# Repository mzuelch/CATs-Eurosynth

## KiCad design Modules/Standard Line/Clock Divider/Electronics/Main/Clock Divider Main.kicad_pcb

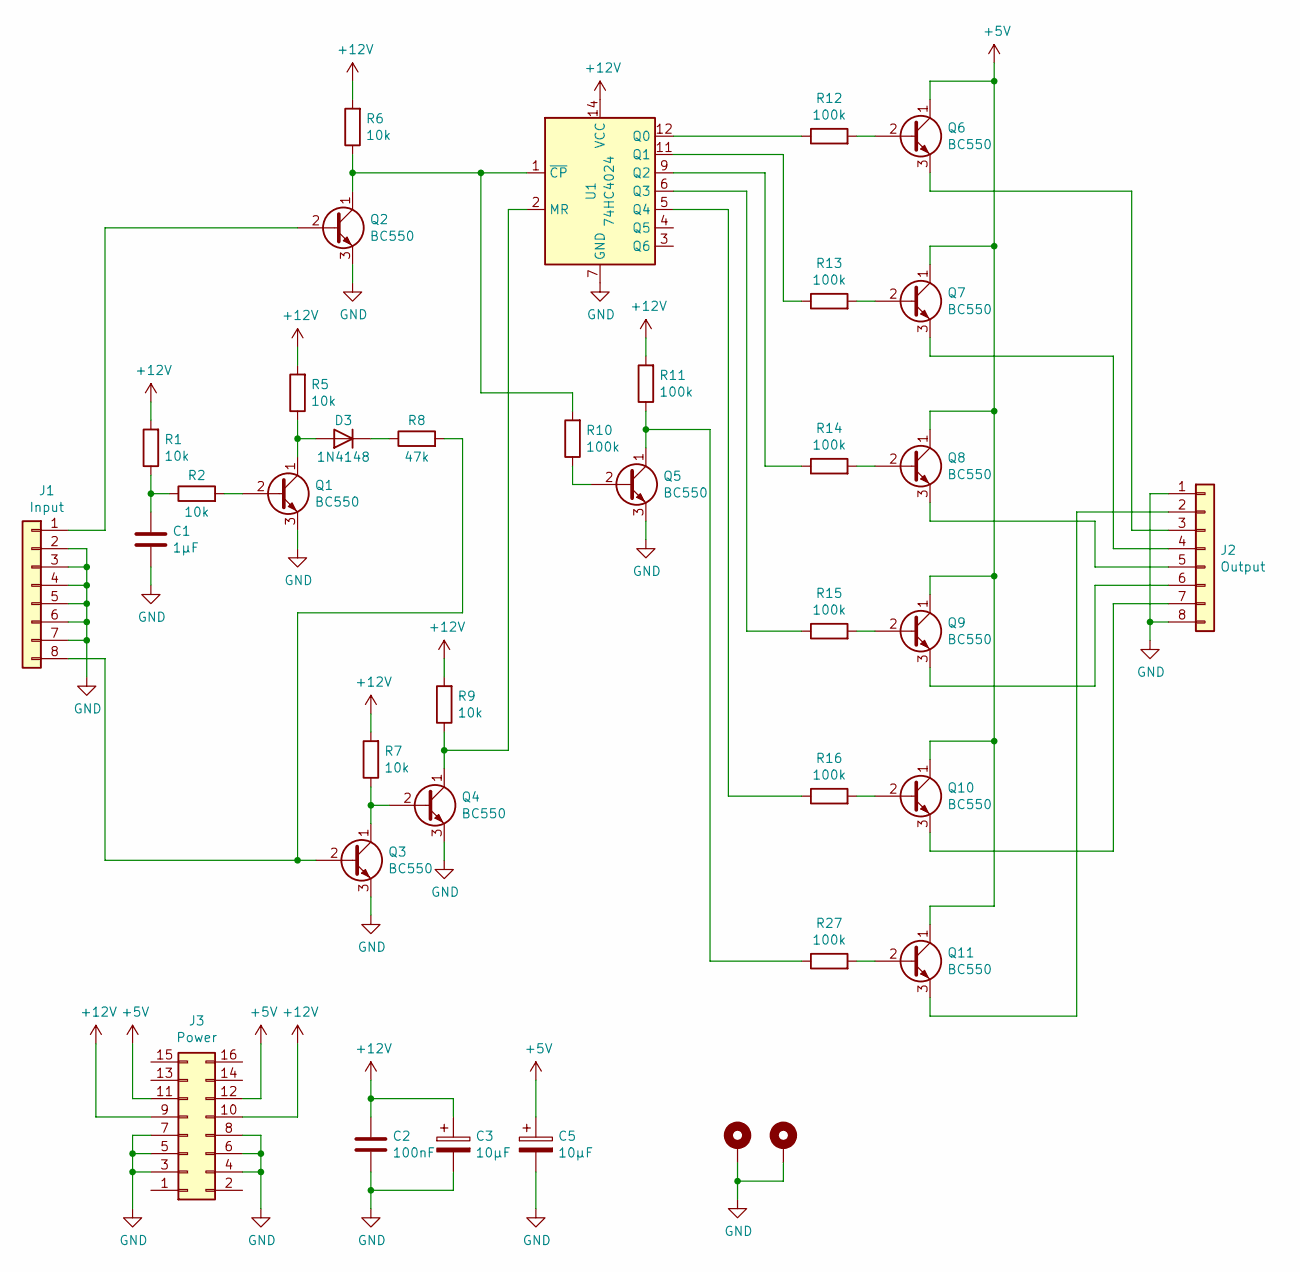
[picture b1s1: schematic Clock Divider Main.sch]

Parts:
C1: 1µF; C_Disc_D6.0mm_W2.5mm_P5.00mm
C2: 100nF; C_Disc_D5.0mm_W2.5mm_P5.00mm
C3, C5: 10µF; CP_Radial_D5.0mm_P2.50mm
D3: 1N4148; D_DO-35_SOD27_P7.62mm_Horizontal
H1, H2: MountingHole_Pad; MountingHole_2.7mm_M2.5_DIN965_Pad
J1: Input; PinHeader_1x08_P2.54mm_Vertical
J2: Output; PinHeader_1x08_P2.54mm_Vertical
J3: Power; IDC-Header_2x08_P2.54mm_Vertical
Q1, Q2, Q3, Q4, Q5, Q6, Q7, Q8, Q9, Q10, Q11: BC550; TO-92_Inline
R1, R2, R5, R6, R7, R9: 10k; R_Axial_DIN0207_L6.3mm_D2.5mm_P7.62mm_Horizontal
R8: 47k; R_Axial_DIN0207_L6.3mm_D2.5mm_P7.62mm_Horizontal
R10, R11, R12, R13, R14, R15, R16, R27: 100k; R_Axial_DIN0207_L6.3mm_D2.5mm_P7.62mm_Horizontal
U1: 74HC4024; DIP-14_W7.62mm_LongPads

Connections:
+5V: C5.1, J3.11, J3.12, Q6.1 (C), Q7.1 (C), Q8.1 (C), Q9.1 (C), Q10.1 (C), Q11.1 (C)
+12V: C2.1, C3.1, J3.9, J3.10, R1.2, R5.2, R6.2, R7.2, R9.2, R11.2, U1.14 (VCC)
GND: C1.2, C2.2, C3.2, C5.2, H1.1, H2.1, J1.2, J1.3, J1.4, J1.5, J1.6, J1.7, J2.1, J2.8, J3.3, J3.4, J3.5, J3.6, J3.7, J3.8, Q1.3 (E), Q2.3 (E), Q3.3 (E), Q4.3 (E), Q5.3 (E), U1.7 (GND)
unnamed: C1.1, R1.1, R2.1
unnamed: D3.1 (K), R8.1
unnamed: D3.2 (A), Q1.1 (C), R5.1
unnamed: J1.1, Q2.2 (B)
unnamed: J1.8, Q3.2 (B), R8.2
unnamed: J2.2, Q11.3 (E)
unnamed: J2.3, Q6.3 (E)
unnamed: J2.4, Q7.3 (E)
unnamed: J2.5, Q8.3 (E)
unnamed: J2.6, Q9.3 (E)
unnamed: J2.7, Q10.3 (E)
unnamed: Q1.2 (B), R2.2
unnamed: Q2.1 (C), R6.1, R10.2, U1.1 (~CP)
unnamed: Q3.1 (C), Q4.2 (B), R7.1
unnamed: Q4.1 (C), R9.1, U1.2 (MR)
unnamed: Q5.1 (C), R11.1, R27.1
unnamed: Q5.2 (B), R10.1
unnamed: Q6.2 (B), R12.2
unnamed: Q7.2 (B), R13.2
unnamed: Q8.2 (B), R14.2
unnamed: Q9.2 (B), R15.2
unnamed: Q10.2 (B), R16.2
unnamed: Q11.2 (B), R27.2
unnamed: R12.1, U1.12 (Q0)
unnamed: R13.1, U1.11 (Q1)
unnamed: R14.1, U1.9 (Q2)
unnamed: R15.1, U1.6 (Q3)
unnamed: R16.1, U1.5 (Q4)

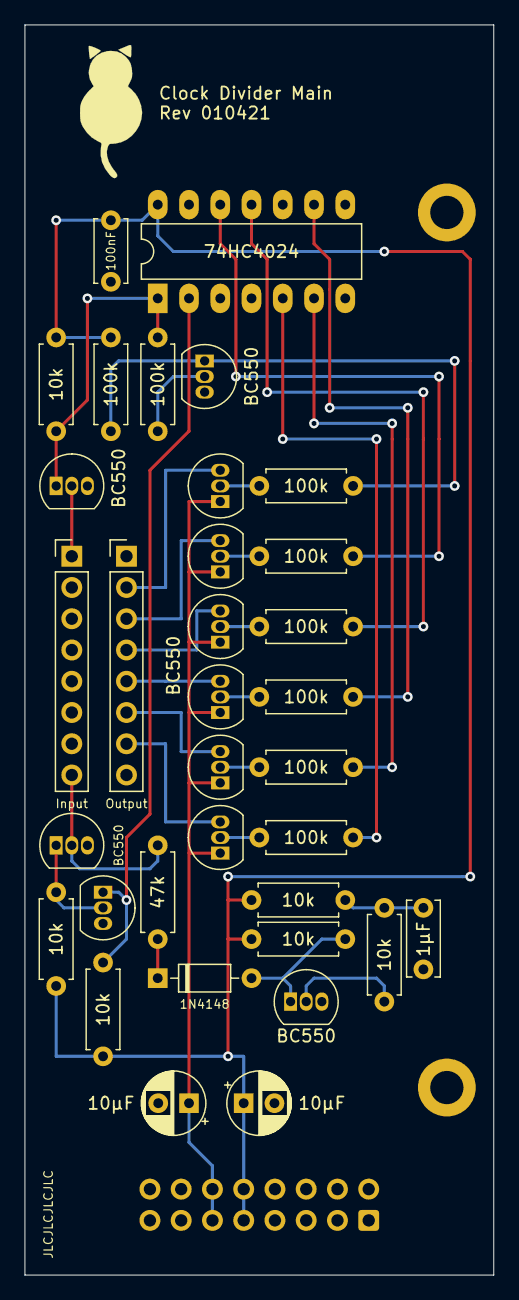
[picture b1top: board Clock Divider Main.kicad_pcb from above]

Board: 2 copper layers, 38.1 x 101.6 mm, 37 parts (1 on the bottom side), 31 nets.

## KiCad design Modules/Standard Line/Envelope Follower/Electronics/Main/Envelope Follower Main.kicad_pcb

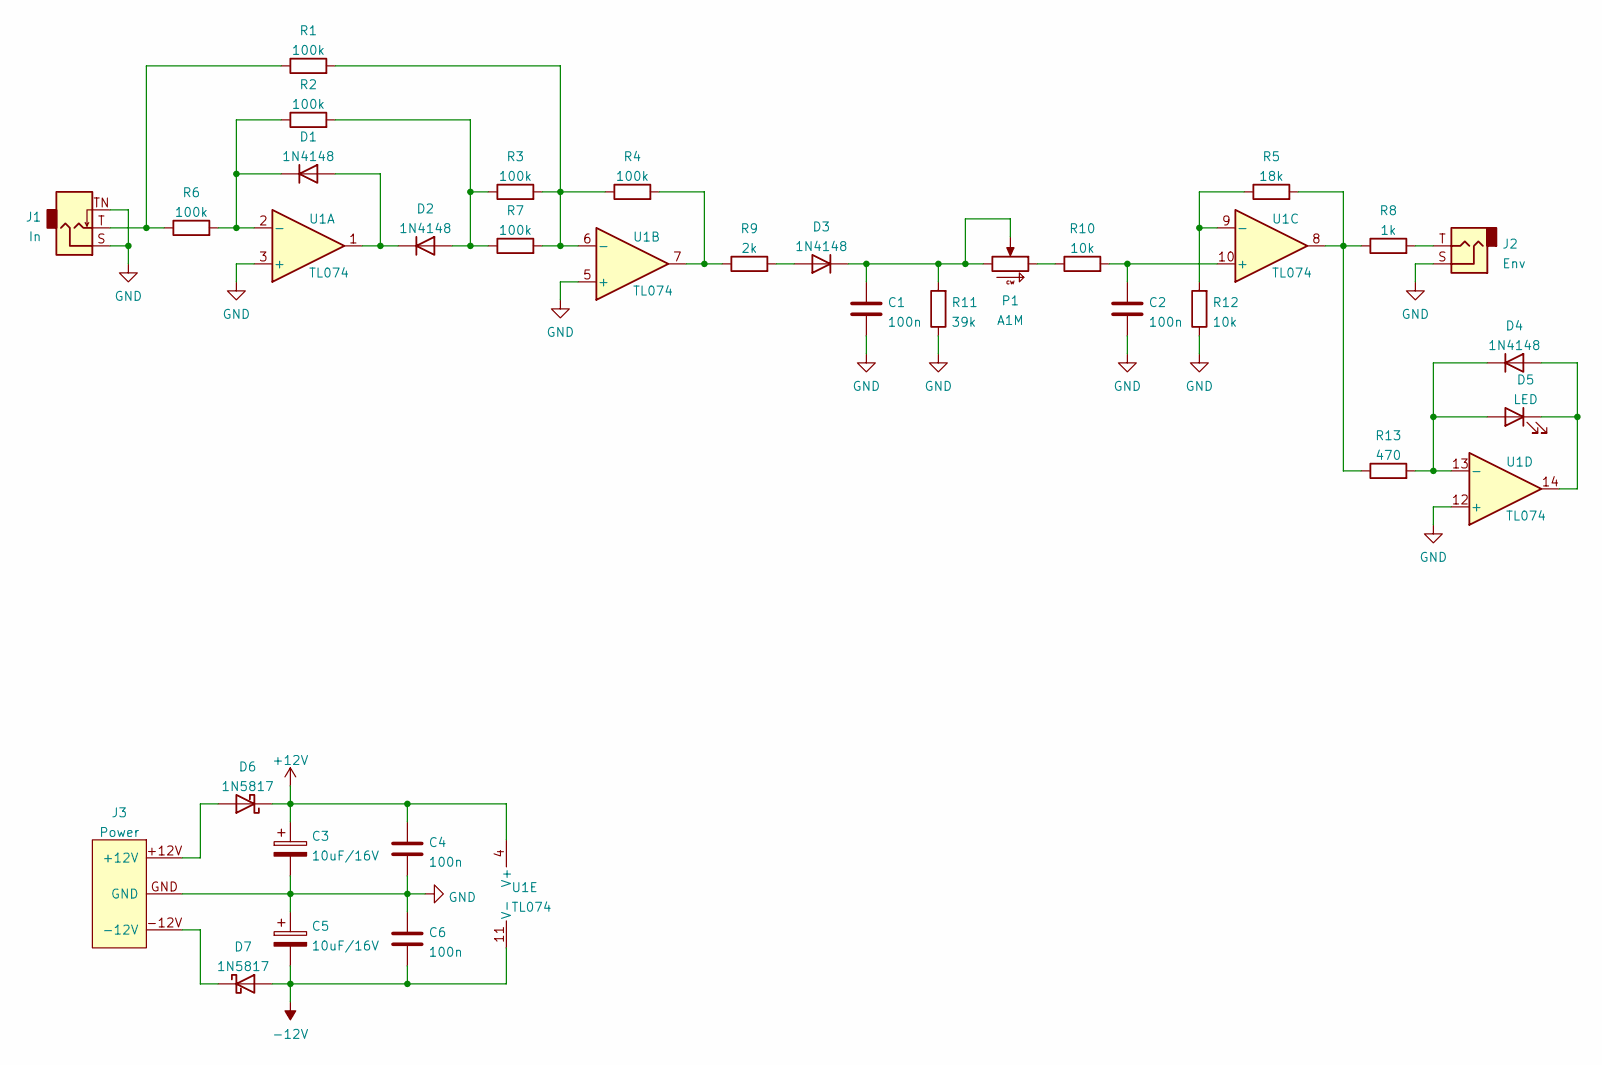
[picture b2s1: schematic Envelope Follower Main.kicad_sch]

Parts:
C1, C2, C4, C6: 100n; C_Disc_D4.7mm_W2.5mm_P5.00mm
C3, C5: 10uF/16V; CP_Radial_D5.0mm_P2.00mm
D1, D2, D3, D4: 1N4148; D_DO-35_SOD27_P7.62mm_Horizontal
D5: LED; LED_D3.0mm_Horizontal_O1.27mm_Z10.0mm
D6, D7: 1N5817; D_DO-41_SOD81_P10.16mm_Horizontal
J1: In; Jack_3.5mm_QingPu_WQP-PJ323M
J2: Env; Jack_3.5mm_QingPu_WQP-PJ323M
J3: Power; Power_2x5_Vertical
P1: A1M; Potentiometer_AlpsAlpine_RK0971110
R1, R2, R3, R4, R6, R7: 100k; R_Axial_DIN0207_L6.3mm_D2.5mm_P7.62mm_Horizontal
R5: 18k; R_Axial_DIN0207_L6.3mm_D2.5mm_P7.62mm_Horizontal
R8: 1k; R_Axial_DIN0207_L6.3mm_D2.5mm_P7.62mm_Horizontal
R9: 2k; R_Axial_DIN0207_L6.3mm_D2.5mm_P7.62mm_Horizontal
R10, R12: 10k; R_Axial_DIN0207_L6.3mm_D2.5mm_P7.62mm_Horizontal
R11: 39k; R_Axial_DIN0207_L6.3mm_D2.5mm_P7.62mm_Horizontal
R13: 470; R_Axial_DIN0207_L6.3mm_D2.5mm_P7.62mm_Horizontal
U1: TL074; DIP-14_W7.62mm_LongPads

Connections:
+12V: C3.1, C4.1, D6.1 (K), U1.4 (V+)
-12V: C5.2, C6.2, D7.2 (A), U1.11 (V-)
GND: C1.2, C2.2, C3.2, C4.2, C5.1, C6.1, J1.S, J1.TN, J2.S, J3.GND, R11.1, R12.1, U1.3 (+), U1.5 (+), U1.12 (+)
unnamed: C1.1, D3.1 (K), P1.CCW, P1.W, R11.2
unnamed: C2.1, R10.2, U1.10 (+)
unnamed: D1.1 (K), R2.1, R6.2, U1.2 (-)
unnamed: D1.2 (A), D2.1 (K), U1.1
unnamed: D2.2 (A), R2.2, R3.1, R7.1
unnamed: D3.2 (A), R9.2
unnamed: D4.1 (K), D5.2 (A), R13.2, U1.13 (-)
unnamed: D4.2 (A), D5.1 (K), U1.14
unnamed: D6.2 (A), J3.+12V
unnamed: D7.1 (K), J3.-12V
unnamed: J1.T, R1.1, R6.1
unnamed: J2.T, R8.2
unnamed: P1.CW, R10.1
unnamed: R1.2, R3.2, R4.1, R7.2, U1.6 (-)
unnamed: R4.2, R9.1, U1.7
unnamed: R5.1, R12.2, U1.9 (-)
unnamed: R5.2, R8.1, R13.1, U1.8

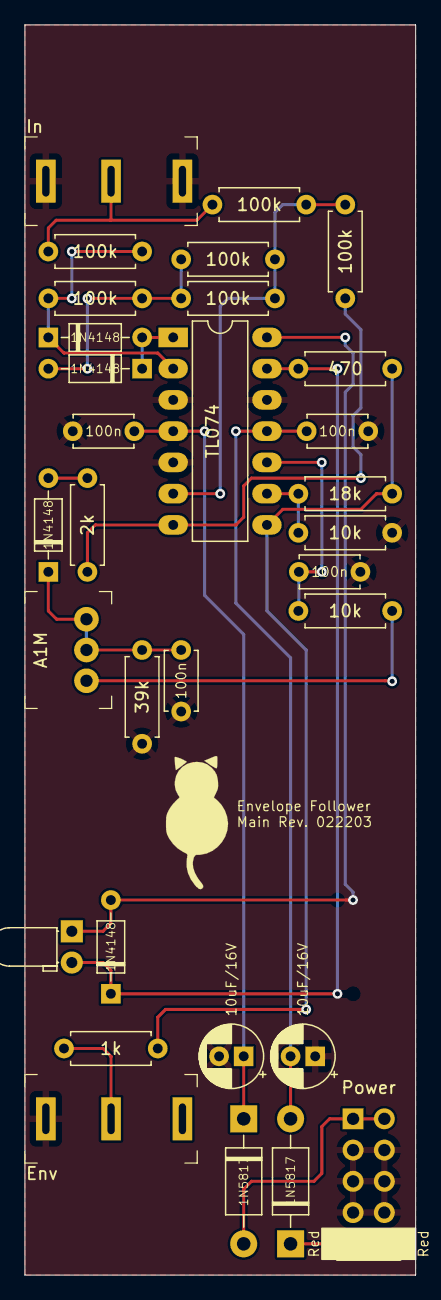
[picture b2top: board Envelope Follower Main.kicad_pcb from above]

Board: 2 copper layers, 31.8 x 101.6 mm, 31 parts (0 on the bottom side), 20 nets.

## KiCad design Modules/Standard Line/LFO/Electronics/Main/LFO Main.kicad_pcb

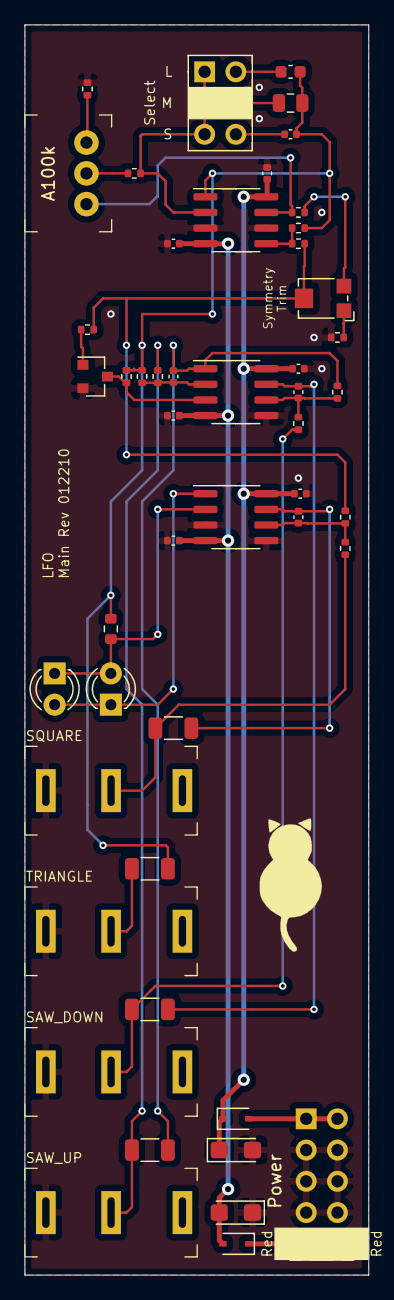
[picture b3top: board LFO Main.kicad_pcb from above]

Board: 2 copper layers, 27.9 x 101.6 mm, 49 parts (0 on the bottom side), 31 nets.

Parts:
C1: 1µF; C_0402_1005Metric
C2, C3: 10µF; CP_EIA-3216-18_Kemet-A
C4, C5, C6, C7, C8, C9: 100n; C_0402_1005Metric
C10: 10µF; C_0603_1608Metric
C11: 2.2µF; C_0805_2012Metric
C12, C13, C14: 10p; C_0402_1005Metric
D1, D2: LED; LED_D3.0mm
D3, D4: 1N5819WS; D_SOD-323
J1: SAW_UP; Jack_3.5mm_QingPu_WQP-PJ323M
J2: SAW_DOWN; Jack_3.5mm_QingPu_WQP-PJ323M
J3: TRIANGLE; Jack_3.5mm_QingPu_WQP-PJ323M
J4: SQUARE; Jack_3.5mm_QingPu_WQP-PJ323M
J5: Power; Power_2x5_Vertical
J6: Select; PinHeader_2x03_P2.54mm_Vertical
Q1: MMBT3904; SOT-23
R1: 47; R_0402_1005Metric
R2: 68k; R_0402_1005Metric
R4, R5, R9, R10, R11, R13, R14, R19, R20: 100k; R_0402_1005Metric
R6, R7: 2k; R_0402_1005Metric
R8: 47k; R_0402_1005Metric
R12, R15, R16, R17: 1k; R_1206_3216Metric
R18: 2k7; R_0603_1608Metric
RV1: A100k; Potentiometer_AlpsAlpine_RK0971110
T1: 1k; Potentiometer_Bourns_TC33X_Vertical
U1, U2, U3: TL072; SOIC-8_3.9x4.9mm_P1.27mm

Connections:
+12V: C2.1, C4.1, C6.1, C8.1, D3.1, U1.8, U2.8, U3.8
+12VA: D3.2, J5.+12V
-12V: C3.2, C5.2, C7.2, C9.2, D4.2, U1.4, U2.4, U3.4
-12VA: D4.1, J5.-12V
GND: C2.2, C3.1, C4.2, C5.1, C6.2, C7.1, C8.2, C9.1, J1.S, J2.S, J3.S, J4.S, J5.GND, Q1.2, R1.1, R7.1, U1.3, U1.6, U2.5, U3.3, U3.5
unnamed: C1.2, J6.6
unnamed: C10.2, J6.2
unnamed: C11.2, J6.4
unnamed: C12.1, R12.2, R14.2, U2.1
unnamed: C12.2, R9.1, R11.2, U2.2
unnamed: C13.1, R15.2, U2.7
unnamed: C13.2, R13.2, R14.1, U2.6
unnamed: C14.1, R17.2, U3.7
unnamed: C14.2, R19.2, R20.1, U3.6
unnamed: D1.1, D2.2, U3.1
unnamed: D1.2, D2.1, R18.2, U3.2
unnamed: J1.T, R11.1, R12.1
unnamed: J2.T, R13.1, R15.1
unnamed: J3.T, R16.1
unnamed: J4.T, R17.1, R19.1
unnamed: J6.1, J6.3, J6.5, R2.1, U1.2
unnamed: Q1.1, R8.1
unnamed: Q1.3, R10.1, U2.3
unnamed: R1.2, RV1.CCW
unnamed: R2.2, RV1.W
unnamed: R4.1, R5.2, U1.5
unnamed: R6.1, T1.3
unnamed: R6.2, RV1.CW, U1.7
unnamed: R7.2, T1.1
SQR: R5.1, R8.2, R20.2, T1.2
TRI: C1.1, C10.1, C11.1, R4.2, R9.2, R10.2, R16.2, R18.1, U1.1

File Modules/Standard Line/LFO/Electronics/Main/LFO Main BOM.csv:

Comment;Designator;Footprint;LCSC
1µF;C1;Capacitor_SMD:C_0402_1005Metric;C52923
10µF;C10;Capacitor_SMD:C_0603_1608Metric;C96446
2,2µF;C11;Capacitor_SMD:C_0805_2012Metric;C49217
10p;C12,C13,C14;Capacitor_SMD:C_0402_1005Metric;C32949
10µF;C2,C3;Capacitor_Tantalum_SMD:CP_EIA-3216-18_Kemet-A;C7171
100n;C4,C5,C6,C7,C8,C9;Capacitor_SMD:C_0402_1005Metric;C307331
LED;D1,D2;LED_THT:LED_D3,0mm;
1N5819WS;D3,D4;Diode_SMD:D_SOD-323;C191023
SAW_UP;J1;Connector_Audio_QingPu:Jack_3,5mm_QingPu_WQP-PJ323M;
SAW_DOWN;J2;Connector_Audio_QingPu:Jack_3,5mm_QingPu_WQP-PJ323M;
TRIANGLE;J3;Connector_Audio_QingPu:Jack_3,5mm_QingPu_WQP-PJ323M;
SQUARE;J4;Connector_Audio_QingPu:Jack_3,5mm_QingPu_WQP-PJ323M;
Power;J5;CATs_Eurosynth_Specials:Power_2x5_Vertical;
Select;J6;Connector_PinHeader_2,54mm:PinHeader_2x03_P2,54mm_Vertical;
MMBT3904;Q1;Package_TO_SOT_SMD:SOT-23;C20526
47;R1;Resistor_SMD:R_0402_1005Metric;C25118
1k;R12,R15,R16,R17;Resistor_SMD:R_1206_3216Metric;C4410
2k7;R18;Resistor_SMD:R_0603_1608Metric;C13167
68k;R2;Resistor_SMD:R_0402_1005Metric;C36871
100k;R4,R5,R9,R10,R11,R13,R14,R19,R20;Resistor_SMD:R_0402_1005Metric;C25741
2k;R6,R7;Resistor_SMD:R_0402_1005Metric;C4109
47k;R8;Resistor_SMD:R_0402_1005Metric;C25792
A100k;RV1;Potentiometer_THT_Additional:Potentiometer_AlpsAlpine_RK0971110;
1k;T1;Potentiometer_SMD:Potentiometer_Bourns_TC33X_Vertical;C719174
TL072;U1,U2,U3;Package_SO:SOIC-8_3,9x4,9mm_P1,27mm;C6961

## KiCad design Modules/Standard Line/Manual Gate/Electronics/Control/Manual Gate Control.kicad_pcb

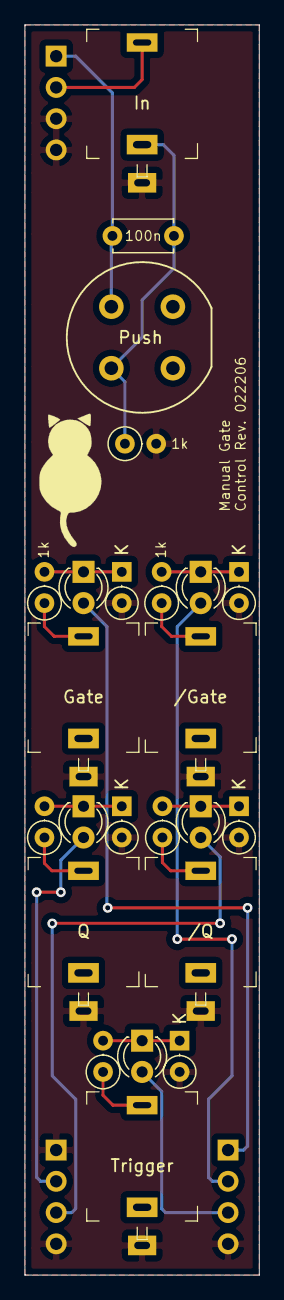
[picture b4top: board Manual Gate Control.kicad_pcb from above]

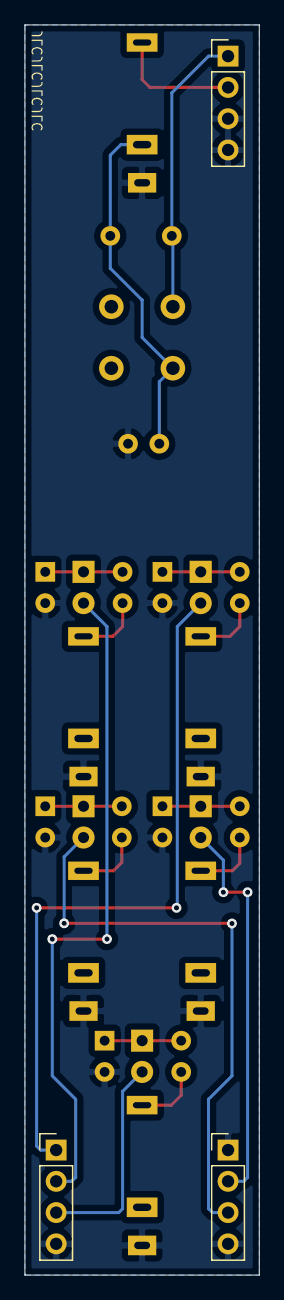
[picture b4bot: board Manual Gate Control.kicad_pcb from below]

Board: 2 copper layers, 19.1 x 101.6 mm, 27 parts (3 on the bottom side), 19 nets.

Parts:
C1: 100n; C_Disc_D4.7mm_W2.5mm_P5.00mm
D1, D2, D5, D7, D8: 1N4733A; D_DO-35_SOD27_P2.54mm_Vertical_KathodeUp
D3, D4, D6, D10, D11: LED; LED_D3.0mm
J1: Q; Jack_3.5mm_QingPu_WQP-PJ301M-12
J2: Trigger; Jack_3.5mm_QingPu_WQP-PJ301M-12
J4: /Q; Jack_3.5mm_QingPu_WQP-PJ301M-12
J5: Gate; Jack_3.5mm_QingPu_WQP-PJ301M-12
J6: /Gate; Jack_3.5mm_QingPu_WQP-PJ301M-12
J7: In; Jack_3.5mm_QingPu_WQP-PJ301M-12
J8: In; PinHeader_1x04_P2.54mm_Vertical
J9: Q_Qq; PinHeader_1x04_P2.54mm_Vertical
J10: Gate; PinHeader_1x04_P2.54mm_Vertical
R1, R13, R15, R26, R34, R38: 1k; R_Axial_DIN0207_L6.3mm_D2.5mm_P2.54mm_Vertical
SW1: Push; Push_E-Switch_KS01Q01

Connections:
+12V: C1.1, J8.1, SW1.2
GND: D1.2, D2.2, D5.2, D7.2, D8.2, J1.S, J2.S, J4.S, J5.S, J6.S, J7.S, J8.3, J8.4, J9.1, J9.4, J10.4, R1.2
Gate_Pin: D10.2, J10.1
Gateq_Pin: D11.2, J10.2
In_Pin: J7.T, J8.2
unnamed: C1.2, J7.TN, R1.1, SW1.1
unnamed: D1.1, D11.1, R38.2
unnamed: D2.1, D3.1, R13.2
unnamed: D4.1, D8.1, R15.2
unnamed: D5.1, D6.1, R26.2
unnamed: D7.1, D10.1, R34.2
unnamed: J1.T, R13.1
unnamed: J2.T, R15.1
unnamed: J4.T, R26.1
unnamed: J5.T, R34.1
unnamed: J6.T, R38.1
Q_Pin: D3.2, J9.2
Qq_Pin: D6.2, J9.3
Trigger_Pin: D4.2, J10.3

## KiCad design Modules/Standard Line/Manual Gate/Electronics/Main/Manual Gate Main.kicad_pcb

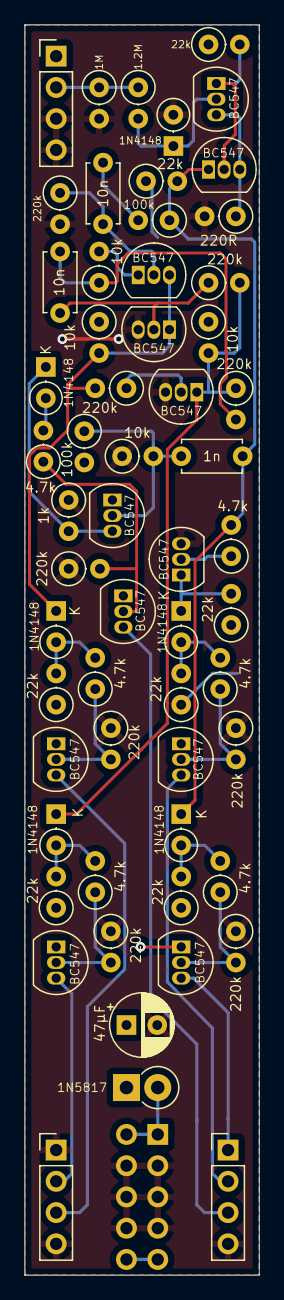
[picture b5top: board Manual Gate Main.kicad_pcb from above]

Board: 2 copper layers, 19.1 x 101.6 mm, 59 parts (1 on the bottom side), 35 nets.

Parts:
C2: 1n; C_Disc_D4.7mm_W2.5mm_P5.00mm
C3, C4: 10n; C_Disc_D4.7mm_W2.5mm_P5.00mm
C5: 47µF; CP_Radial_D5.0mm_P2.50mm
D1, D2, D5, D8, D9, D12: 1N4148; D_DO-35_SOD27_P2.54mm_Vertical_KathodeUp
D7: 1N5817; D_DO-41_SOD81_P2.54mm_Vertical_KathodeUp
J3: Power; Power_2x5_Vertical
J8: In; PinHeader_1x04_P2.54mm_Vertical
J9: Q_Qq; PinHeader_1x04_P2.54mm_Vertical
J10: Gate; PinHeader_1x04_P2.54mm_Vertical
Q1, Q2, Q3, Q4, Q5, Q6, Q7, Q8, Q9, Q10, Q11, Q12: BC547; TO-92_Inline
R1, R3: 100k; R_Axial_DIN0207_L6.3mm_D2.5mm_P2.54mm_Vertical
R2, R16, R18, R23: 10k; R_Axial_DIN0207_L6.3mm_D2.5mm_P2.54mm_Vertical
R4: 1k; R_Axial_DIN0207_L6.3mm_D2.5mm_P2.54mm_Vertical
R5, R19, R27, R31, R33, R41, R43: 22k; R_Axial_DIN0207_L6.3mm_D2.5mm_P2.54mm_Vertical
R6, R10, R21, R28, R29, R35: 4.7k; R_Axial_DIN0207_L6.3mm_D2.5mm_P2.54mm_Vertical
R8, R9, R11, R17, R20, R22, R25, R30, R36: 220k; R_Axial_DIN0207_L6.3mm_D2.5mm_P2.54mm_Vertical
R39: 1M; R_Axial_DIN0207_L6.3mm_D2.5mm_P2.54mm_Vertical
R40: 1.2M; R_Axial_DIN0207_L6.3mm_D2.5mm_P2.54mm_Vertical
R42: 220R; R_Axial_DIN0207_L6.3mm_D2.5mm_P2.54mm_Vertical

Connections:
+12V: C5.1, D7.1, J8.1, Q1.1, Q3.1, Q4.1, Q7.1, Q9.1, Q10.1, R1.2, R5.1, R16.1, R19.1, R23.1, R27.1, R31.1, R33.1, R41.1, R43.1
+12VA: D7.2, J3.+12V
GND: C5.2, D12.2, J3.GND, J8.3, J8.4, J9.1, J9.4, J10.4, Q5.3, Q6.3, Q8.3, R2.1, R4.1, R8.2, R9.1, R11.1, R22.1, R30.1, R36.1, R39.2, R42.2
Gate_Pin: J10.1, Q9.3
Gateq_Pin: J10.2, Q10.3
In_Pin: J8.2, R39.1, R40.1
unnamed: C2.1, Q1.2, R1.1, R2.2
unnamed: C3.1, Q2.2, R8.1
unnamed: C3.2, R3.2
unnamed: C4.1, R18.1, R25.2
unnamed: C4.2, Q5.2, R20.1
unnamed: D1.2, R5.2, R6.2
unnamed: D2.1, Q1.3, R4.2
unnamed: D2.2, R10.2
unnamed: D5.2, R19.2, R21.2
unnamed: D8.2, R27.2, R29.2
unnamed: D9.1, Q8.1, R31.2
unnamed: D9.2, R33.2, R35.2
unnamed: D12.1, Q11.2, R40.2
unnamed: Q2.1, R18.2
unnamed: Q3.2, R6.1, R9.2
unnamed: Q4.2, R10.1, R11.2
unnamed: Q6.2, R17.1
unnamed: Q7.2, R21.1, R22.2
unnamed: Q8.2, R28.1
unnamed: Q9.2, R29.1, R30.2
unnamed: Q10.2, R35.1, R36.2
unnamed: Q11.1, Q12.2, R41.2
unnamed: Q11.3, Q12.3, R42.1
Ping: C2.2, D8.1, Q12.1, R3.1, R28.2, R43.2
Q: D1.1, Q6.1, R20.2, R23.2, R25.1
Q_Pin: J9.2, Q3.3
Qq_Pin: J9.3, Q7.3
Qquer: D5.1, Q2.3, Q5.1, R16.2, R17.2
Trigger_Pin: J10.3, Q4.3
